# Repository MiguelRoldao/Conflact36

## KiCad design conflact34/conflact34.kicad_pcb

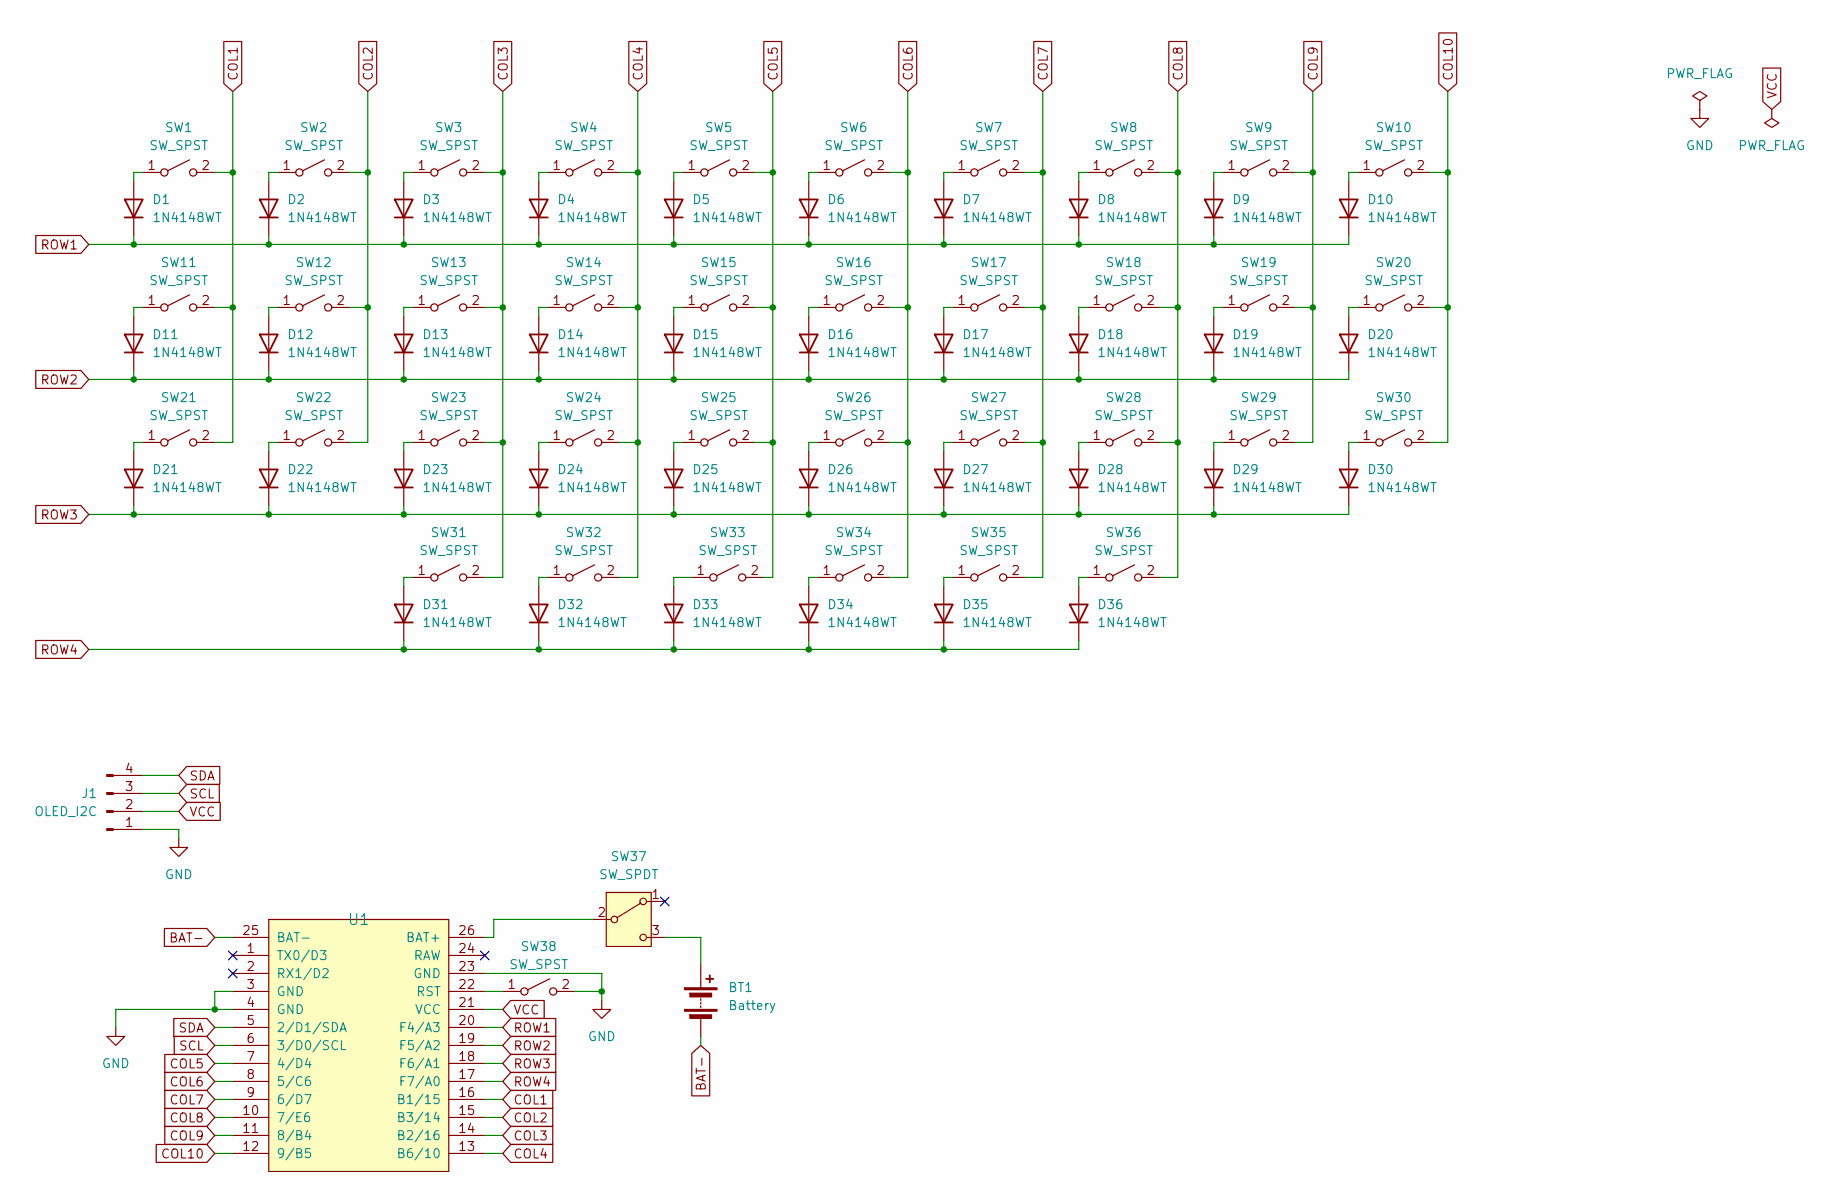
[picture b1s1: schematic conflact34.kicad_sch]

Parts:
BT1: Battery; PinHeader_1x02_P2.54mm_Vertical
D1, D2, D3, D4, D5, D6, D7, D8, D9, D10, D11, D12, D13, D14, D15, D16, D17, D18, D19, D20, D21, D22, D23, D24, D25, D26, D27, D28, D29, D30, D31, D32, D33, D34, D35, D36: 1N4148WT; D_SOD-123
J1: OLED_I2C; PinHeader_1x04_P2.54mm_Vertical
SW1, SW2, SW3, SW4, SW5, SW6, SW7, SW8, SW9, SW10, SW11, SW12, SW13, SW14, SW15, SW16, SW17, SW18, SW19, SW20, SW21, SW22, SW23, SW24, SW25, SW26, SW27, SW28, SW29, SW30, SW31, SW32, SW33, SW34, SW35, SW36: SW_SPST; SW_Universal_TH
SW37: SW_SPDT; SW_SMD_MSK12C02
SW38: SW_SPST; SW_SMD_EVQP7C01K
U1: U_ProMicro_nRF52840_TH_L

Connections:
COL1: SW1.2 (B), SW11.2 (B), SW21.2 (B), U1.16 (B1/15)
COL2: SW2.2 (B), SW12.2 (B), SW22.2 (B), U1.15 (B3/14)
COL3: SW3.2 (B), SW13.2 (B), SW23.2 (B), SW31.2 (B), U1.14 (B2/16)
COL4: SW4.2 (B), SW14.2 (B), SW24.2 (B), SW32.2 (B), U1.13 (B6/10)
COL5: SW5.2 (B), SW15.2 (B), SW25.2 (B), SW33.2 (B), U1.7 (4/D4)
COL6: SW6.2 (B), SW16.2 (B), SW26.2 (B), SW34.2 (B), U1.8 (5/C6)
COL7: SW7.2 (B), SW17.2 (B), SW27.2 (B), SW35.2 (B), U1.9 (6/D7)
COL8: SW8.2 (B), SW18.2 (B), SW28.2 (B), SW36.2 (B), U1.10 (7/E6)
COL9: SW9.2 (B), SW19.2 (B), SW29.2 (B), U1.11 (8/B4)
COL10: SW10.2 (B), SW20.2 (B), SW30.2 (B), U1.12 (9/B5)
GND: J1.1, SW38.2 (B), U1.3 (GND), U1.4 (GND), U1.23 (GND)
unnamed: D1.2 (A), SW1.1 (A)
unnamed: D2.2 (A), SW2.1 (A)
unnamed: D3.2 (A), SW3.1 (A)
unnamed: D4.2 (A), SW4.1 (A)
unnamed: D5.2 (A), SW5.1 (A)
unnamed: D6.2 (A), SW6.1 (A)
unnamed: D7.2 (A), SW7.1 (A)
unnamed: D8.2 (A), SW8.1 (A)
unnamed: D9.2 (A), SW9.1 (A)
unnamed: D10.2 (A), SW10.1 (A)
unnamed: D11.2 (A), SW11.1 (A)
unnamed: D12.2 (A), SW12.1 (A)
unnamed: D13.2 (A), SW13.1 (A)
unnamed: D14.2 (A), SW14.1 (A)
unnamed: D15.2 (A), SW15.1 (A)
unnamed: D16.2 (A), SW16.1 (A)
unnamed: D17.2 (A), SW17.1 (A)
unnamed: D18.2 (A), SW18.1 (A)
unnamed: D19.2 (A), SW19.1 (A)
unnamed: D20.2 (A), SW20.1 (A)
unnamed: D21.2 (A), SW21.1 (A)
unnamed: D22.2 (A), SW22.1 (A)
unnamed: D23.2 (A), SW23.1 (A)
unnamed: D24.2 (A), SW24.1 (A)
unnamed: D25.2 (A), SW25.1 (A)
unnamed: D26.2 (A), SW26.1 (A)
unnamed: D27.2 (A), SW27.1 (A)
unnamed: D28.2 (A), SW28.1 (A)
unnamed: D29.2 (A), SW29.1 (A)
unnamed: D30.2 (A), SW30.1 (A)
unnamed: D31.2 (A), SW31.1 (A)
unnamed: D32.2 (A), SW32.1 (A)
unnamed: D33.2 (A), SW33.1 (A)
unnamed: D34.2 (A), SW34.1 (A)
unnamed: D35.2 (A), SW35.1 (A)
unnamed: D36.2 (A), SW36.1 (A)
unnamed: SW37.2 (B), U1.26 (BAT+)
unnamed: SW38.1 (A), U1.22 (RST)
ROW1: D1.1 (K), D2.1 (K), D3.1 (K), D4.1 (K), D5.1 (K), D6.1 (K), D7.1 (K), D8.1 (K), D9.1 (K), D10.1 (K), U1.20 (F4/A3)
ROW2: D11.1 (K), D12.1 (K), D13.1 (K), D14.1 (K), D15.1 (K), D16.1 (K), D17.1 (K), D18.1 (K), D19.1 (K), D20.1 (K), U1.19 (F5/A2)
ROW3: D21.1 (K), D22.1 (K), D23.1 (K), D24.1 (K), D25.1 (K), D26.1 (K), D27.1 (K), D28.1 (K), D29.1 (K), D30.1 (K), U1.18 (F6/A1)
ROW4: D31.1 (K), D32.1 (K), D33.1 (K), D34.1 (K), D35.1 (K), D36.1 (K), U1.17 (F7/A0)
SCL: J1.3, U1.6 (3/D0/SCL)
SDA: J1.4, U1.5 (2/D1/SDA)
VCC: J1.2, U1.21 (VCC)

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
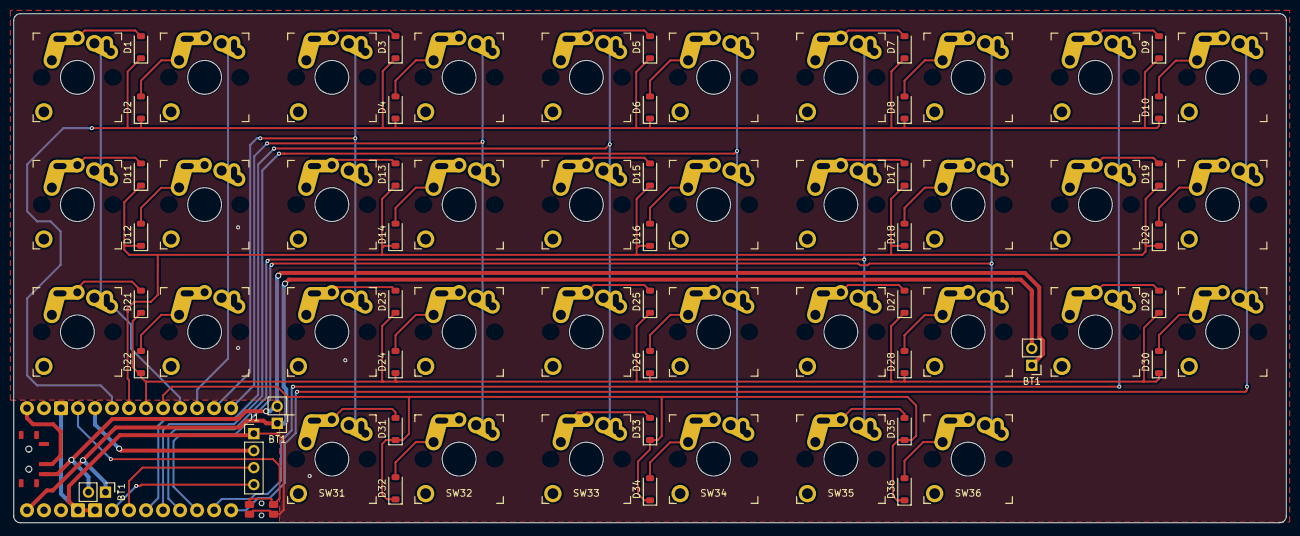
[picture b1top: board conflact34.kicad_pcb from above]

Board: 2 copper layers, 190.0 x 76.0 mm, 79 parts (0 on the bottom side), 58 nets.

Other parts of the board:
BT1#2, BT1#3: Battery; PinHeader_1x02_P2.54mm_Vertical
